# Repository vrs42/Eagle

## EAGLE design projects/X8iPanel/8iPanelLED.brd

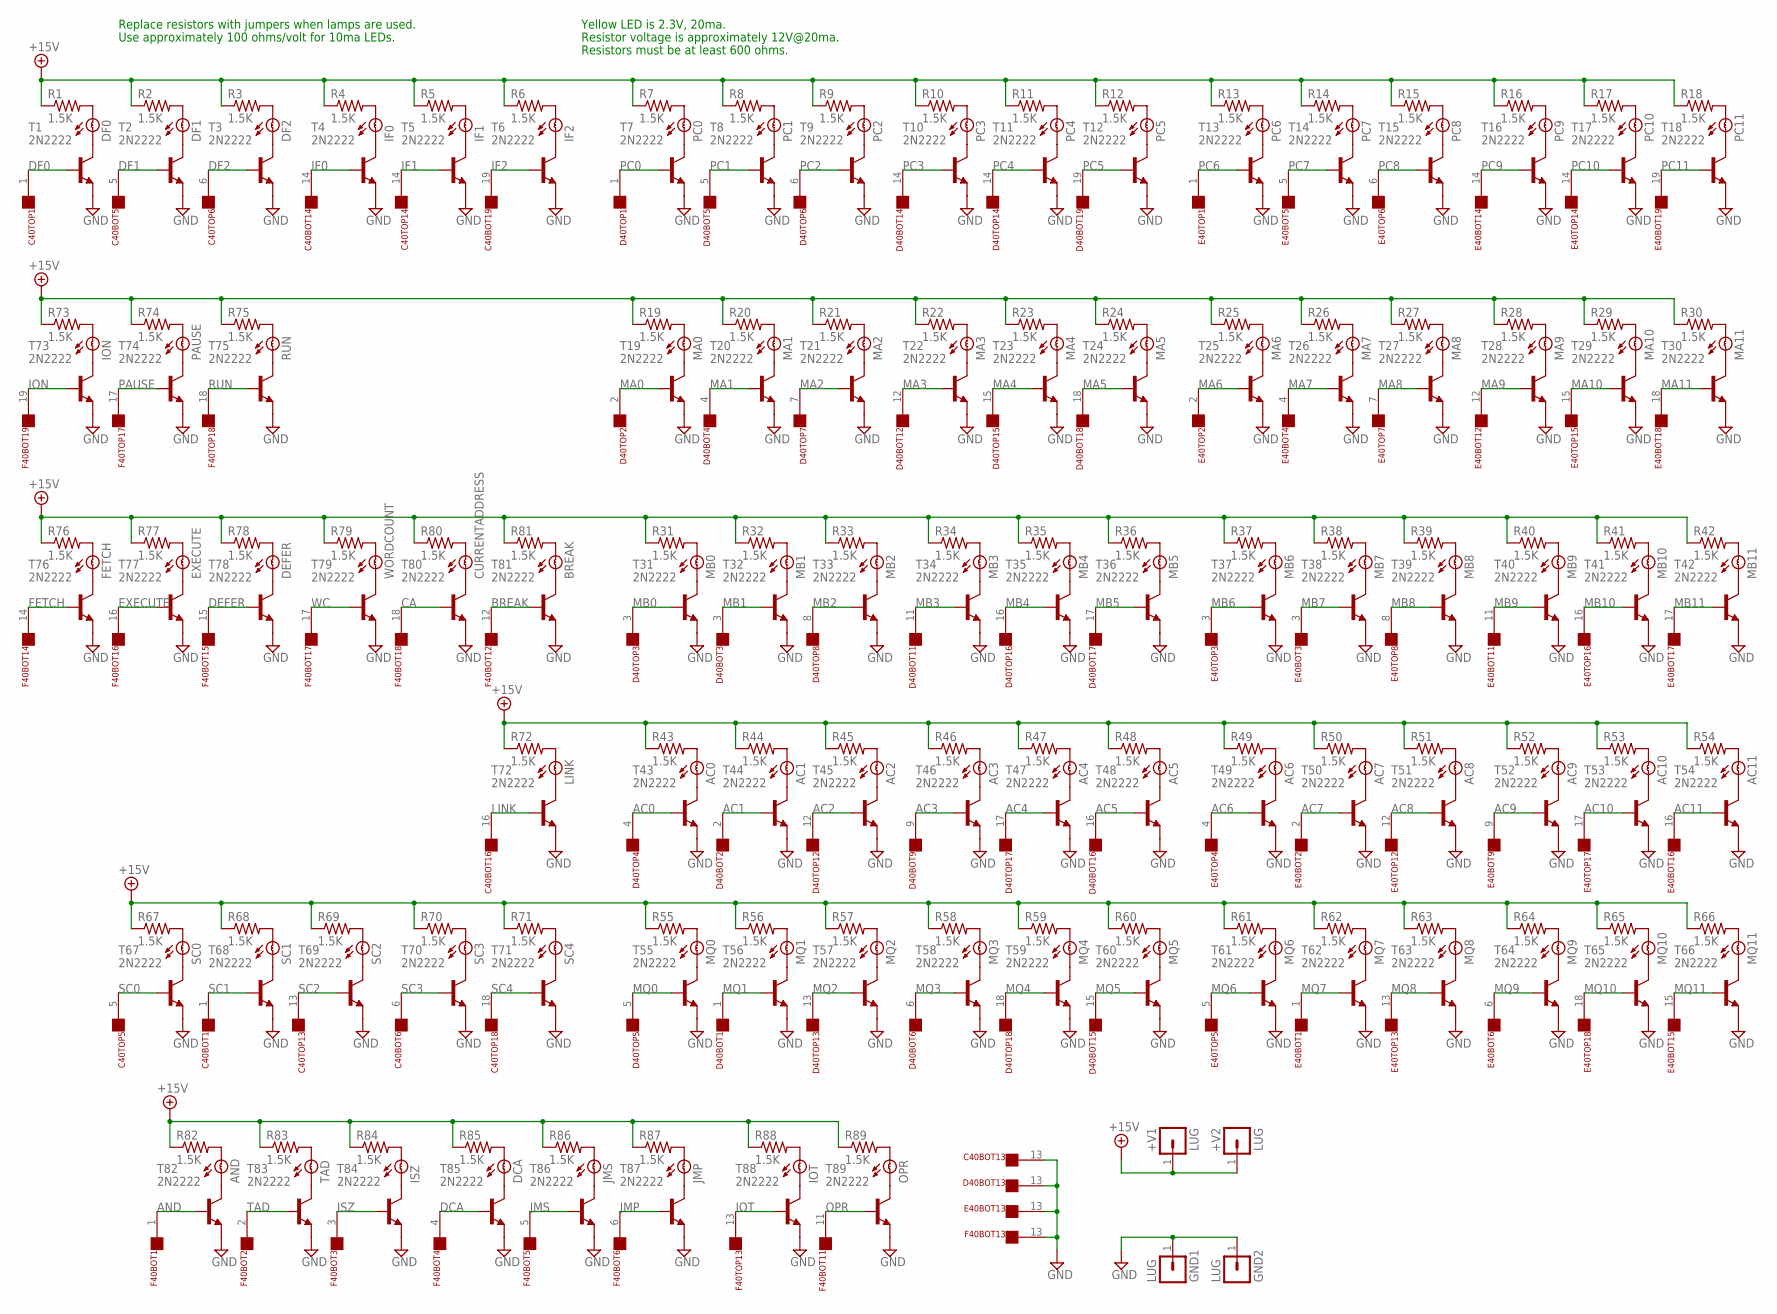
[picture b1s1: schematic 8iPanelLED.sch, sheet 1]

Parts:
+V1, +V2: LUG; SPADELUG
AC0, AC1, AC2, AC3, AC4, AC5, AC6, AC7, AC8, AC9, AC10, AC11: BULB
AND: BULB
BREAK: BULB
C40BOT, C40TOP: FLEX19
CURRENTADDRESS: BULB
D40BOT, D40TOP: FLEX19
DCA: BULB
DEFER: BULB
DF0, DF1, DF2: BULB
E40BOT, E40TOP: FLEX19
EXECUTE: BULB
F40BOT, F40TOP: FLEX19
FETCH: BULB
GND1, GND2: LUG; SPADELUG
IF0, IF1, IF2: BULB
ION: BULB
IOT: BULB
ISZ: BULB
JMP: BULB
JMS: BULB
LINK: BULB
MA0, MA1, MA2, MA3, MA4, MA5, MA6, MA7, MA8, MA9, MA10, MA11: BULB
MB0, MB1, MB2, MB3, MB4, MB5, MB6, MB7, MB8, MB9, MB10, MB11: BULB
MQ0, MQ1, MQ2, MQ3, MQ4, MQ5, MQ6, MQ7, MQ8, MQ9, MQ10, MQ11: BULB
OPR: BULB
PAUSE: BULB
PC0, PC1, PC2, PC3, PC4, PC5, PC6, PC7, PC8, PC9, PC10, PC11: BULB
R1, R2, R3, R4, R5, R6, R7, R8, R9, R10, R11, R12, R13, R14, R15, R16, R17, R18, R19, R20, R21, R22, R23, R24, R25, R26, R27, R28, R29, R30, R31, R32, R33, R34, R35, R36, R37, R38, R39, R40, R41, R42, R43, R44, R45, R46, R47, R48, R49, R50, R51, R52, R53, R54, R55, R56, R57, R58, R59, R60, R61, R62, R63, R64, R65, R66, R67, R68, R69, R70, R71, R72, R73, R74, R75, R76, R77, R78, R79, R80, R81, R82, R83, R84, R85, R86, R87, R88, R89: 1.5K; 0207/10
RUN: BULB
SC0, SC1, SC2, SC3, SC4: BULB
T1, T2, T3, T4, T5, T6, T7, T8, T9, T10, T11, T12, T13, T14, T15, T16, T17, T18, T19, T20, T21, T22, T23, T24, T25, T26, T27, T28, T29, T30, T31, T32, T33, T34, T35, T36, T37, T38, T39, T40, T41, T42, T43, T44, T45, T46, T47, T48, T49, T50, T51, T52, T53, T54, T55, T56, T57, T58, T59, T60, T61, T62, T63, T64, T65, T66, T67, T68, T69, T70, T71, T72, T73, T74, T75, T76, T77, T78, T79, T80, T81, T82, T83, T84, T85, T86, T87, T88, T89: 2N2222; TO92
TAD: BULB
WORDCOUNT: BULB

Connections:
+15V: +V1.1, +V2.1, R1.1, R2.1, R3.1, R4.1, R5.1, R6.1, R7.1, R8.1, R9.1, R10.1, R11.1, R12.1, R13.1, R14.1, R15.1, R16.1, R17.1, R18.1, R19.1, R20.1, R21.1, R22.1, R23.1, R24.1, R25.1, R26.1, R27.1, R28.1, R29.1, R30.1, R31.1, R32.1, R33.1, R34.1, R35.1, R36.1, R37.1, R38.1, R39.1, R40.1, R41.1, R42.1, R43.1, R44.1, R45.1, R46.1, R47.1, R48.1, R49.1, R50.1, R51.1, R52.1, R53.1, R54.1, R55.1, R56.1, R57.1, R58.1, R59.1, R60.1, R61.1, R62.1, R63.1, R64.1, R65.1, R66.1, R67.1, R68.1, R69.1, R70.1, R71.1, R72.1, R73.1, R74.1, R75.1, R76.1, R77.1, R78.1, R79.1, R80.1, R81.1, R82.1, R83.1, R84.1, R85.1, R86.1, R87.1, R88.1, R89.1
AC0: D40TOP.4, T43.2 (B); also elsewhere on the board
AC1: D40BOT.2, T44.2 (B); also elsewhere on the board
AC2: D40TOP.12, T45.2 (B); also elsewhere on the board
AC3: D40BOT.9, T46.2 (B); also elsewhere on the board
AC4: D40TOP.17, T47.2 (B); also elsewhere on the board
AC5: D40BOT.16, T48.2 (B); also elsewhere on the board
AC6: E40TOP.4, T49.2 (B); also elsewhere on the board
AC7: E40BOT.2, T50.2 (B); also elsewhere on the board
AC8: E40TOP.12, T51.2 (B); also elsewhere on the board
AC9: E40BOT.9, T52.2 (B); also elsewhere on the board
AC10: E40TOP.17, T53.2 (B); also elsewhere on the board
AC11: E40BOT.16, T54.2 (B); also elsewhere on the board
AND: F40BOT.1, T82.2 (B); also elsewhere on the board
BREAK: F40BOT.12, T81.2 (B); also elsewhere on the board
CA: F40BOT.18, T80.2 (B); also elsewhere on the board
DCA: F40BOT.4, T85.2 (B); also elsewhere on the board
DEFER: F40BOT.15, T78.2 (B); also elsewhere on the board
DF0: C40TOP.1, T1.2 (B); also elsewhere on the board
DF1: C40BOT.5, T2.2 (B); also elsewhere on the board
DF2: C40TOP.6, T3.2 (B); also elsewhere on the board
EXECUTE: F40BOT.16, T77.2 (B); also elsewhere on the board
FETCH: F40BOT.14, T76.2 (B); also elsewhere on the board
GND: C40BOT.13, D40BOT.13, E40BOT.13, F40BOT.13, GND1.1, GND2.1, T1.1 (E), T2.1 (E), T3.1 (E), T4.1 (E), T5.1 (E), T6.1 (E), T7.1 (E), T8.1 (E), T9.1 (E), T10.1 (E), T11.1 (E), T12.1 (E), T13.1 (E), T14.1 (E), T15.1 (E), T16.1 (E), T17.1 (E), T18.1 (E), T19.1 (E), T20.1 (E), T21.1 (E), T22.1 (E), T23.1 (E), T24.1 (E), T25.1 (E), T26.1 (E), T27.1 (E), T28.1 (E), T29.1 (E), T30.1 (E), T31.1 (E), T32.1 (E), T33.1 (E), T34.1 (E), T35.1 (E), T36.1 (E), T37.1 (E), T38.1 (E), T39.1 (E), T40.1 (E), T41.1 (E), T42.1 (E), T43.1 (E), T44.1 (E), T45.1 (E), T46.1 (E), T47.1 (E), T48.1 (E), T49.1 (E), T50.1 (E), T51.1 (E), T52.1 (E), T53.1 (E), T54.1 (E), T55.1 (E), T56.1 (E), T57.1 (E), T58.1 (E), T59.1 (E), T60.1 (E), T61.1 (E), T62.1 (E), T63.1 (E), T64.1 (E), T65.1 (E), T66.1 (E), T67.1 (E), T68.1 (E), T69.1 (E), T70.1 (E), T71.1 (E), T72.1 (E), T73.1 (E), T74.1 (E), T75.1 (E), T76.1 (E), T77.1 (E), T78.1 (E), T79.1 (E), T80.1 (E), T81.1 (E), T82.1 (E), T83.1 (E), T84.1 (E), T85.1 (E), T86.1 (E), T87.1 (E), T88.1 (E), T89.1 (E); also elsewhere on the board
IF0: C40BOT.14, T4.2 (B); also elsewhere on the board
IF1: C40TOP.14, T5.2 (B); also elsewhere on the board
IF2: C40BOT.19, T6.2 (B); also elsewhere on the board
ION: F40BOT.19, T73.2 (B); also elsewhere on the board
IOT: F40TOP.13, T88.2 (B); also elsewhere on the board
ISZ: F40BOT.3, T84.2 (B); also elsewhere on the board
JMP: F40BOT.6, T87.2 (B); also elsewhere on the board
JMS: F40BOT.5, T86.2 (B); also elsewhere on the board
LINK: C40BOT.16, T72.2 (B); also elsewhere on the board
MA0: D40TOP.2, T19.2 (B); also elsewhere on the board
MA1: D40BOT.4, T20.2 (B); also elsewhere on the board
MA2: D40TOP.7, T21.2 (B); also elsewhere on the board
MA3: D40BOT.12, T22.2 (B); also elsewhere on the board
MA4: D40TOP.15, T23.2 (B); also elsewhere on the board
MA5: D40BOT.18, T24.2 (B); also elsewhere on the board
MA6: E40TOP.2, T25.2 (B); also elsewhere on the board
MA7: E40BOT.4, T26.2 (B); also elsewhere on the board
MA8: E40TOP.7, T27.2 (B); also elsewhere on the board
MA9: E40BOT.12, T28.2 (B); also elsewhere on the board
MA10: E40TOP.15, T29.2 (B); also elsewhere on the board
MA11: E40BOT.18, T30.2 (B); also elsewhere on the board
MB0: D40TOP.3, T31.2 (B); also elsewhere on the board
MB1: D40BOT.3, T32.2 (B); also elsewhere on the board
MB2: D40TOP.8, T33.2 (B); also elsewhere on the board
MB3: D40BOT.11, T34.2 (B); also elsewhere on the board
MB4: D40TOP.16, T35.2 (B); also elsewhere on the board
MB5: D40BOT.17, T36.2 (B); also elsewhere on the board
MB6: E40TOP.3, T37.2 (B); also elsewhere on the board
MB7: E40BOT.3, T38.2 (B); also elsewhere on the board
MB8: E40TOP.8, T39.2 (B); also elsewhere on the board
MB9: E40BOT.11, T40.2 (B); also elsewhere on the board
MB10: E40TOP.16, T41.2 (B); also elsewhere on the board
MB11: E40BOT.17, T42.2 (B); also elsewhere on the board
MQ0: D40TOP.5, T55.2 (B); also elsewhere on the board
MQ1: D40BOT.1, T56.2 (B); also elsewhere on the board
MQ2: D40TOP.13, T57.2 (B); also elsewhere on the board
MQ3: D40BOT.6, T58.2 (B); also elsewhere on the board
MQ4: D40TOP.18, T59.2 (B); also elsewhere on the board
MQ5: D40BOT.15, T60.2 (B); also elsewhere on the board
MQ6: E40TOP.5, T61.2 (B); also elsewhere on the board
MQ7: E40BOT.1, T62.2 (B); also elsewhere on the board
MQ8: E40TOP.13, T63.2 (B); also elsewhere on the board
MQ9: E40BOT.6, T64.2 (B); also elsewhere on the board
MQ10: E40TOP.18, T65.2 (B); also elsewhere on the board
MQ11: E40BOT.15, T66.2 (B); also elsewhere on the board
unnamed: DF0.B, T1.3 (C)
unnamed: DF1.B, T2.3 (C)
unnamed: DF2.B, T3.3 (C)
unnamed: IF0.B, T4.3 (C)
unnamed: IF1.B, T5.3 (C)
unnamed: IF2.B, T6.3 (C)
unnamed: PC0.B, T7.3 (C)
unnamed: PC1.B, T8.3 (C)
unnamed: PC2.B, T9.3 (C)
unnamed: PC3.B, T10.3 (C)
unnamed: PC4.B, T11.3 (C)
unnamed: PC5.B, T12.3 (C)
unnamed: PC6.B, T13.3 (C)
unnamed: PC7.B, T14.3 (C)
unnamed: PC8.B, T15.3 (C)
unnamed: PC9.B, T16.3 (C)
unnamed: PC10.B, T17.3 (C)
unnamed: PC11.B, T18.3 (C)
unnamed: MA0.B, T19.3 (C)
unnamed: MA1.B, T20.3 (C)
unnamed: MA2.B, T21.3 (C)
unnamed: MA3.B, T22.3 (C)
unnamed: MA4.B, T23.3 (C)
unnamed: MA5.B, T24.3 (C)
unnamed: MA6.B, T25.3 (C)
unnamed: MA7.B, T26.3 (C)
unnamed: MA8.B, T27.3 (C)
unnamed: MA9.B, T28.3 (C)
unnamed: MA10.B, T29.3 (C)
unnamed: MA11.B, T30.3 (C)
unnamed: MB0.B, T31.3 (C)
unnamed: MB1.B, T32.3 (C)
unnamed: MB2.B, T33.3 (C)
unnamed: MB3.B, T34.3 (C)
unnamed: MB4.B, T35.3 (C)
unnamed: MB5.B, T36.3 (C)
unnamed: MB6.B, T37.3 (C)
unnamed: MB7.B, T38.3 (C)
unnamed: MB8.B, T39.3 (C)
unnamed: MB9.B, T40.3 (C)
unnamed: MB10.B, T41.3 (C)
unnamed: MB11.B, T42.3 (C)
unnamed: AC0.B, T43.3 (C)
unnamed: AC1.B, T44.3 (C)
unnamed: AC2.B, T45.3 (C)
unnamed: AC3.B, T46.3 (C)
unnamed: AC4.B, T47.3 (C)
unnamed: AC5.B, T48.3 (C)
unnamed: AC6.B, T49.3 (C)
unnamed: AC7.B, T50.3 (C)
unnamed: AC8.B, T51.3 (C)
unnamed: AC9.B, T52.3 (C)
unnamed: AC10.B, T53.3 (C)
unnamed: AC11.B, T54.3 (C)
unnamed: MQ0.B, T55.3 (C)
unnamed: MQ1.B, T56.3 (C)
unnamed: MQ2.B, T57.3 (C)
unnamed: MQ3.B, T58.3 (C)
unnamed: MQ4.B, T59.3 (C)
unnamed: MQ5.B, T60.3 (C)
unnamed: MQ6.B, T61.3 (C)
unnamed: MQ7.B, T62.3 (C)
unnamed: MQ8.B, T63.3 (C)
unnamed: MQ9.B, T64.3 (C)
unnamed: MQ10.B, T65.3 (C)
unnamed: MQ11.B, T66.3 (C)
unnamed: SC0.B, T67.3 (C)
unnamed: SC1.B, T68.3 (C)
unnamed: SC2.B, T69.3 (C)
unnamed: SC3.B, T70.3 (C)
unnamed: SC4.B, T71.3 (C)
unnamed: LINK.B, T72.3 (C)
unnamed: ION.B, T73.3 (C)
unnamed: PAUSE.B, T74.3 (C)
unnamed: RUN.B, T75.3 (C)
unnamed: FETCH.B, T76.3 (C)
unnamed: EXECUTE.B, T77.3 (C)
unnamed: DEFER.B, T78.3 (C)
unnamed: T79.3 (C), WORDCOUNT.B
unnamed: CURRENTADDRESS.B, T80.3 (C)
unnamed: BREAK.B, T81.3 (C)
unnamed: AND.B, T82.3 (C)
unnamed: T83.3 (C), TAD.B
unnamed: ISZ.B, T84.3 (C)
unnamed: DCA.B, T85.3 (C)
unnamed: JMS.B, T86.3 (C)
unnamed: JMP.B, T87.3 (C)
unnamed: IOT.B, T88.3 (C)
unnamed: OPR.B, T89.3 (C)
unnamed: DF0.A, R1.2
unnamed: DF1.A, R2.2
unnamed: DF2.A, R3.2
unnamed: IF0.A, R4.2
unnamed: IF1.A, R5.2
unnamed: IF2.A, R6.2
unnamed: PC0.A, R7.2
unnamed: PC1.A, R8.2
unnamed: PC2.A, R9.2
unnamed: PC3.A, R10.2
unnamed: PC4.A, R11.2
unnamed: PC5.A, R12.2
unnamed: PC6.A, R13.2
unnamed: PC7.A, R14.2
unnamed: PC8.A, R15.2
unnamed: PC9.A, R16.2
unnamed: PC10.A, R17.2
unnamed: PC11.A, R18.2
unnamed: ION.A, R73.2
unnamed: PAUSE.A, R74.2
unnamed: R75.2, RUN.A
unnamed: MA0.A, R19.2
unnamed: MA1.A, R20.2
unnamed: MA2.A, R21.2
unnamed: MA3.A, R22.2
unnamed: MA4.A, R23.2
unnamed: MA5.A, R24.2
unnamed: MA6.A, R25.2
unnamed: MA7.A, R26.2
unnamed: MA8.A, R27.2
unnamed: MA9.A, R28.2
unnamed: MA10.A, R29.2
unnamed: MA11.A, R30.2
unnamed: FETCH.A, R76.2
unnamed: EXECUTE.A, R77.2
unnamed: DEFER.A, R78.2
unnamed: R79.2, WORDCOUNT.A
unnamed: CURRENTADDRESS.A, R80.2
unnamed: BREAK.A, R81.2
unnamed: LINK.A, R72.2
unnamed: MB0.A, R31.2
unnamed: MB1.A, R32.2
unnamed: MB2.A, R33.2
unnamed: MB3.A, R34.2
unnamed: MB4.A, R35.2
unnamed: MB5.A, R36.2
unnamed: MB6.A, R37.2
unnamed: MB7.A, R38.2
unnamed: MB8.A, R39.2
unnamed: MB9.A, R40.2
unnamed: MB10.A, R41.2
unnamed: MB11.A, R42.2
unnamed: AC0.A, R43.2
unnamed: AC1.A, R44.2
unnamed: AC2.A, R45.2
unnamed: AC3.A, R46.2
unnamed: AC4.A, R47.2
unnamed: AC5.A, R48.2
unnamed: AC6.A, R49.2
unnamed: AC7.A, R50.2
unnamed: AC8.A, R51.2
unnamed: AC9.A, R52.2
unnamed: AC10.A, R53.2
unnamed: AC11.A, R54.2
unnamed: R67.2, SC0.A
unnamed: R68.2, SC1.A
unnamed: R69.2, SC2.A
unnamed: R70.2, SC3.A
unnamed: R71.2, SC4.A
unnamed: MQ11.A, R66.2
unnamed: MQ10.A, R65.2
unnamed: MQ9.A, R64.2
unnamed: MQ8.A, R63.2
unnamed: MQ7.A, R62.2
unnamed: MQ6.A, R61.2
unnamed: MQ5.A, R60.2
unnamed: MQ4.A, R59.2
unnamed: MQ3.A, R58.2
unnamed: MQ2.A, R57.2
unnamed: MQ1.A, R56.2
unnamed: MQ0.A, R55.2
unnamed: AND.A, R82.2
unnamed: R83.2, TAD.A
unnamed: ISZ.A, R84.2
unnamed: DCA.A, R85.2
unnamed: JMS.A, R86.2
unnamed: JMP.A, R87.2
unnamed: IOT.A, R88.2
unnamed: OPR.A, R89.2
OPR: F40BOT.11, T89.2 (B); also elsewhere on the board
PAUSE: F40TOP.17, T74.2 (B); also elsewhere on the board
PC0: D40TOP.1, T7.2 (B); also elsewhere on the board
PC1: D40BOT.5, T8.2 (B); also elsewhere on the board
PC2: D40TOP.6, T9.2 (B); also elsewhere on the board
PC3: D40BOT.14, T10.2 (B); also elsewhere on the board
PC4: D40TOP.14, T11.2 (B); also elsewhere on the board
PC5: D40BOT.19, T12.2 (B); also elsewhere on the board
PC6: E40TOP.1, T13.2 (B); also elsewhere on the board
PC7: E40BOT.5, T14.2 (B); also elsewhere on the board
PC8: E40TOP.6, T15.2 (B); also elsewhere on the board
PC9: E40BOT.14, T16.2 (B); also elsewhere on the board
PC10: E40TOP.14, T17.2 (B); also elsewhere on the board
PC11: E40BOT.19, T18.2 (B); also elsewhere on the board
RUN: F40TOP.18, T75.2 (B); also elsewhere on the board
SC0: C40TOP.5, T67.2 (B); also elsewhere on the board
SC1: C40BOT.1, T68.2 (B); also elsewhere on the board
SC2: C40TOP.13, T69.2 (B); also elsewhere on the board
SC3: C40BOT.6, T70.2 (B); also elsewhere on the board
SC4: C40TOP.18, T71.2 (B); also elsewhere on the board
TAD: F40BOT.2, T83.2 (B); also elsewhere on the board
WC: F40BOT.17, T79.2 (B); also elsewhere on the board

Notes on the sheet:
Replace resistors with jumpers when lamps are used.
Use approximately 100 ohms/volt for 10ma LEDs.
Yellow LED is 2.3V, 20ma.
Resistor voltage is approximately 12V@20ma.
Resistors must be at least 600 ohms.

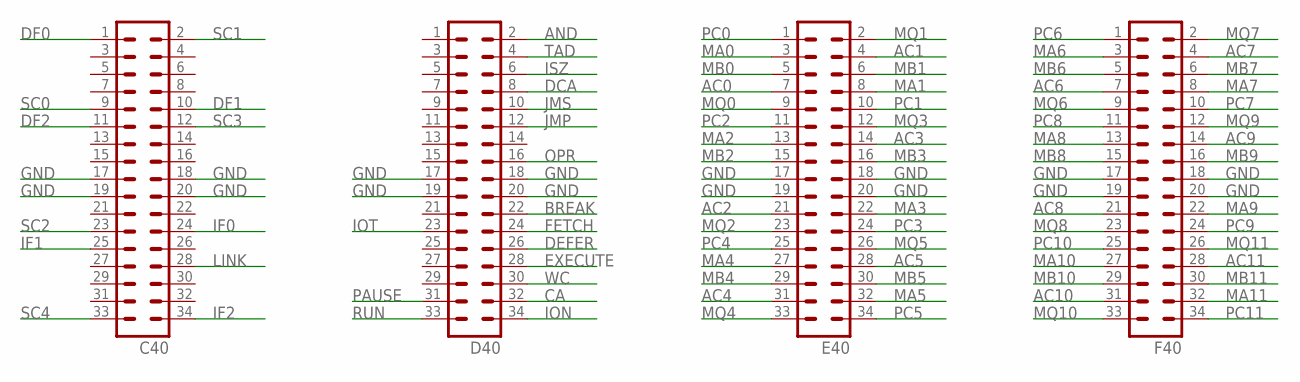
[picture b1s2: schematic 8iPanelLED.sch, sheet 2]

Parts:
C40: MA17-2
D40: MA17-2
E40: MA17-2
F40: MA17-2

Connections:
AC0: E40.7; also elsewhere on the board
AC1: E40.4; also elsewhere on the board
AC2: E40.21; also elsewhere on the board
AC3: E40.14; also elsewhere on the board
AC4: E40.31; also elsewhere on the board
AC5: E40.28; also elsewhere on the board
AC6: F40.7; also elsewhere on the board
AC7: F40.4; also elsewhere on the board
AC8: F40.21; also elsewhere on the board
AC9: F40.14; also elsewhere on the board
AC10: F40.31; also elsewhere on the board
AC11: F40.28; also elsewhere on the board
AND: D40.2; also elsewhere on the board
BREAK: D40.22; also elsewhere on the board
CA: D40.32; also elsewhere on the board
DCA: D40.8; also elsewhere on the board
DEFER: D40.26; also elsewhere on the board
DF0: C40.1; also elsewhere on the board
DF1: C40.10; also elsewhere on the board
DF2: C40.11; also elsewhere on the board
EXECUTE: D40.28; also elsewhere on the board
FETCH: D40.24; also elsewhere on the board
GND: C40.17, C40.18, C40.19, C40.20, D40.17, D40.18, D40.19, D40.20, E40.17, E40.18, E40.19, E40.20, F40.17, F40.18, F40.19, F40.20; also elsewhere on the board
IF0: C40.24; also elsewhere on the board
IF1: C40.25; also elsewhere on the board
IF2: C40.34; also elsewhere on the board
ION: D40.34; also elsewhere on the board
IOT: D40.23; also elsewhere on the board
ISZ: D40.6; also elsewhere on the board
JMP: D40.12; also elsewhere on the board
JMS: D40.10; also elsewhere on the board
LINK: C40.28; also elsewhere on the board
MA0: E40.3; also elsewhere on the board
MA1: E40.8; also elsewhere on the board
MA2: E40.13; also elsewhere on the board
MA3: E40.22; also elsewhere on the board
MA4: E40.27; also elsewhere on the board
MA5: E40.32; also elsewhere on the board
MA6: F40.3; also elsewhere on the board
MA7: F40.8; also elsewhere on the board
MA8: F40.13; also elsewhere on the board
MA9: F40.22; also elsewhere on the board
MA10: F40.27; also elsewhere on the board
MA11: F40.32; also elsewhere on the board
MB0: E40.5; also elsewhere on the board
MB1: E40.6; also elsewhere on the board
MB2: E40.15; also elsewhere on the board
MB3: E40.16; also elsewhere on the board
MB4: E40.29; also elsewhere on the board
MB5: E40.30; also elsewhere on the board
MB6: F40.5; also elsewhere on the board
MB7: F40.6; also elsewhere on the board
MB8: F40.15; also elsewhere on the board
MB9: F40.16; also elsewhere on the board
MB10: F40.29; also elsewhere on the board
MB11: F40.30; also elsewhere on the board
MQ0: E40.9; also elsewhere on the board
MQ1: E40.2; also elsewhere on the board
MQ2: E40.23; also elsewhere on the board
MQ3: E40.12; also elsewhere on the board
MQ4: E40.33; also elsewhere on the board
MQ5: E40.26; also elsewhere on the board
MQ6: F40.9; also elsewhere on the board
MQ7: F40.2; also elsewhere on the board
MQ8: F40.23; also elsewhere on the board
MQ9: F40.12; also elsewhere on the board
MQ10: F40.33; also elsewhere on the board
MQ11: F40.26; also elsewhere on the board
OPR: D40.16; also elsewhere on the board
PAUSE: D40.31; also elsewhere on the board
PC0: E40.1; also elsewhere on the board
PC1: E40.10; also elsewhere on the board
PC2: E40.11; also elsewhere on the board
PC3: E40.24; also elsewhere on the board
PC4: E40.25; also elsewhere on the board
PC5: E40.34; also elsewhere on the board
PC6: F40.1; also elsewhere on the board
PC7: F40.10; also elsewhere on the board
PC8: F40.11; also elsewhere on the board
PC9: F40.24; also elsewhere on the board
PC10: F40.25; also elsewhere on the board
PC11: F40.34; also elsewhere on the board
RUN: D40.33; also elsewhere on the board
SC0: C40.9; also elsewhere on the board
SC1: C40.2; also elsewhere on the board
SC2: C40.23; also elsewhere on the board
SC3: C40.12; also elsewhere on the board
SC4: C40.33; also elsewhere on the board
TAD: D40.4; also elsewhere on the board
WC: D40.30; also elsewhere on the board

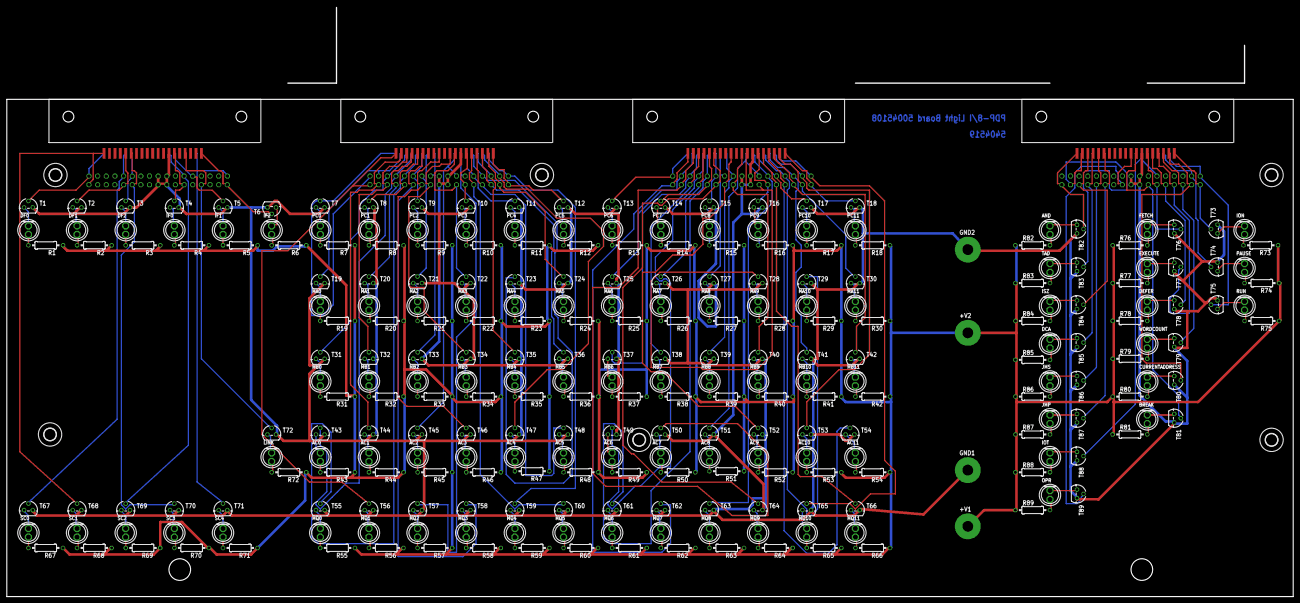
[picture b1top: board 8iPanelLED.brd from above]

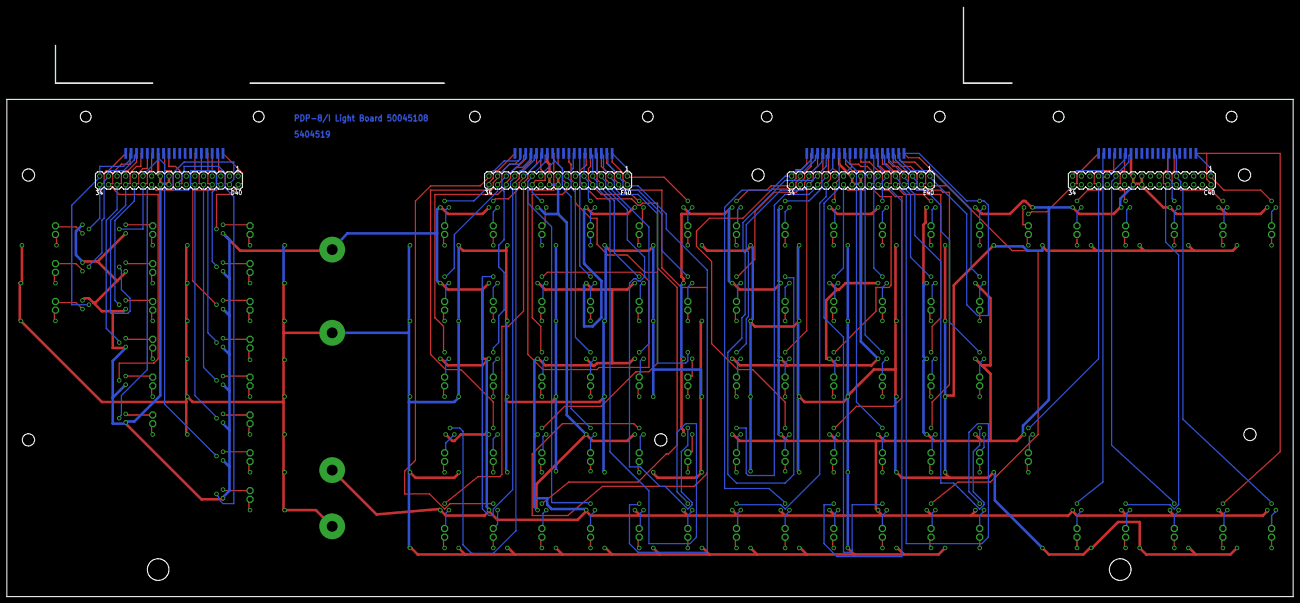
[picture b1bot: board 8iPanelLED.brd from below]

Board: 2 copper layers, 377.8 x 146.1 mm, 293 parts (8 on the bottom side), 269 nets.

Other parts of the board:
U$1, U$2, U$3, U$4: STRAIN-RELIEF
U$5, U$6, U$7, U$8, U$9, U$11: 3,6

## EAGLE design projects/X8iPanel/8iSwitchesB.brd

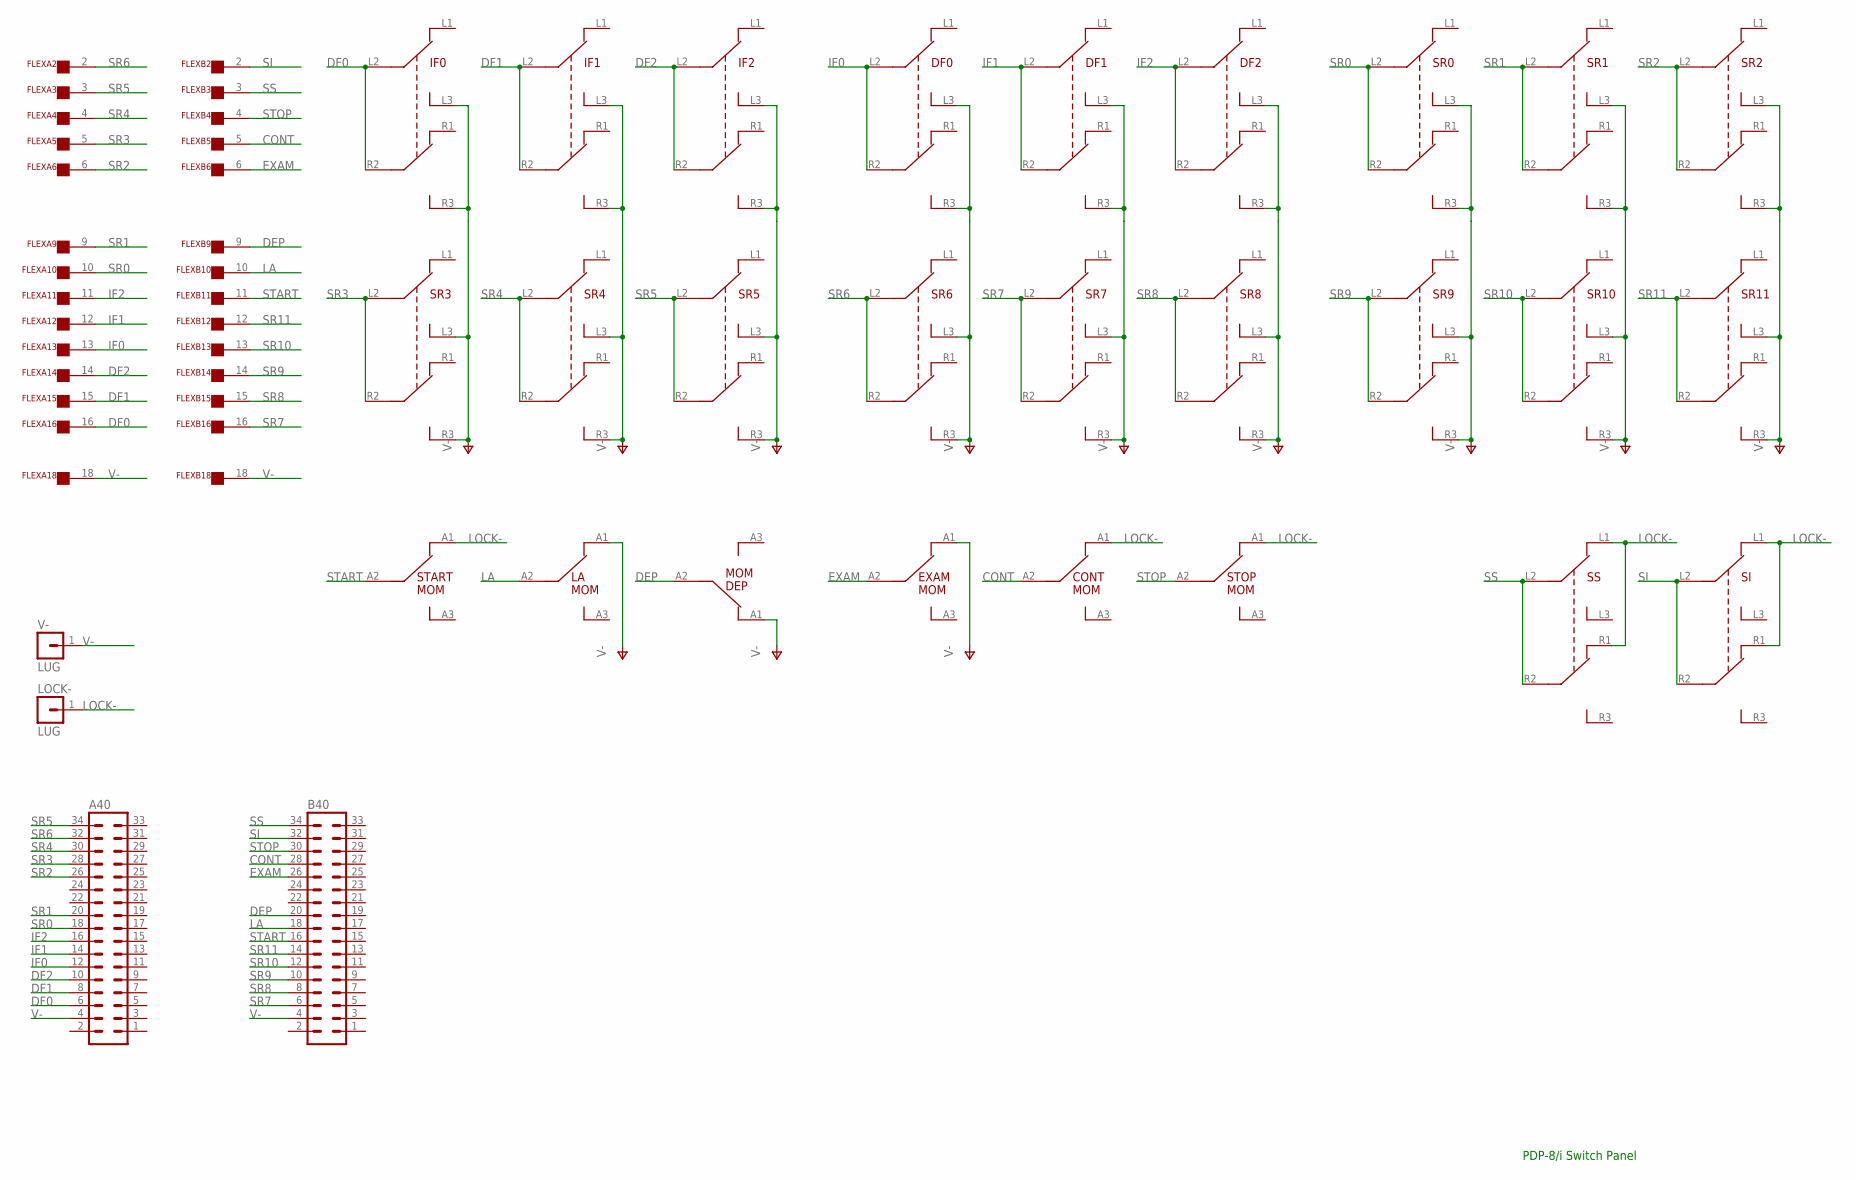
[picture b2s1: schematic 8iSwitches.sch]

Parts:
A40: MA17-2
B40: MA17-2
CONT: SPDT8I
DEP: SPDT8I
DF0, DF1, DF2: DPDT8I
EXAM: SPDT8I
FLEXA: FLEX19
FLEXB: FLEX19
IF0, IF1, IF2: DPDT8I
LA: SPDT8I
LOCK-: LUG; SPADELUG
SI: DPDT8I
SR0, SR1, SR2, SR3, SR4, SR5, SR6, SR7, SR8, SR9, SR10, SR11: DPDT8I
SS: DPDT8I
START: SPDT8I
STOP: SPDT8I
V-: LUG; SPADELUG

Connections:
CONT: B40.28, CONT.A2, FLEXB.5
DEP: B40.20, DEP.A2, FLEXB.9
DF0: A40.6, FLEXA.16, IF0.L2 (A2), IF0.R2 (B2)
DF1: A40.8, FLEXA.15, IF1.L2 (A2), IF1.R2 (B2)
DF2: A40.10, FLEXA.14, IF2.L2 (A2), IF2.R2 (B2)
EXAM: B40.26, EXAM.A2, FLEXB.6
IF0: A40.12, DF0.L2 (A2), DF0.R2 (B2), FLEXA.13
IF1: A40.14, DF1.L2 (A2), DF1.R2 (B2), FLEXA.12
IF2: A40.16, DF2.L2 (A2), DF2.R2 (B2), FLEXA.11
LA: B40.18, FLEXB.10, LA.A2
LOCK-: CONT.A1, LOCK-.1, SI.L1 (A1), SI.R1 (B1), SS.L1 (A1), SS.R1 (B1), START.A1, STOP.A1
SI: B40.32, FLEXB.2, SI.L2 (A2), SI.R2 (B2)
SR0: A40.18, FLEXA.10, SR0.L2 (A2), SR0.R2 (B2)
SR1: A40.20, FLEXA.9, SR1.L2 (A2), SR1.R2 (B2)
SR2: A40.26, FLEXA.6, SR2.L2 (A2), SR2.R2 (B2)
SR3: A40.28, FLEXA.5, SR3.L2 (A2), SR3.R2 (B2)
SR4: A40.30, FLEXA.4, SR4.L2 (A2), SR4.R2 (B2)
SR5: A40.34, FLEXA.3, SR5.L2 (A2), SR5.R2 (B2)
SR6: A40.32, FLEXA.2, SR6.L2 (A2), SR6.R2 (B2)
SR7: B40.6, FLEXB.16, SR7.L2 (A2), SR7.R2 (B2)
SR8: B40.8, FLEXB.15, SR8.L2 (A2), SR8.R2 (B2)
SR9: B40.10, FLEXB.14, SR9.L2 (A2), SR9.R2 (B2)
SR10: B40.12, FLEXB.13, SR10.L2 (A2), SR10.R2 (B2)
SR11: B40.14, FLEXB.12, SR11.L2 (A2), SR11.R2 (B2)
SS: B40.34, FLEXB.3, SS.L2 (A2), SS.R2 (B2)
START: B40.16, FLEXB.11, START.A2
STOP: B40.30, FLEXB.4, STOP.A2
V-: A40.4, B40.4, DEP.A1, DF0.L3 (A3), DF0.R3 (B3), DF1.L3 (A3), DF1.R3 (B3), DF2.L3 (A3), DF2.R3 (B3), EXAM.A1, FLEXA.18, FLEXB.18, IF0.L3 (A3), IF0.R3 (B3), IF1.L3 (A3), IF1.R3 (B3), IF2.L3 (A3), IF2.R3 (B3), LA.A1, SR0.L3 (A3), SR0.R3 (B3), SR1.L3 (A3), SR1.R3 (B3), SR2.L3 (A3), SR2.R3 (B3), SR3.L3 (A3), SR3.R3 (B3), SR4.L3 (A3), SR4.R3 (B3), SR5.L3 (A3), SR5.R3 (B3), SR6.L3 (A3), SR6.R3 (B3), SR7.L3 (A3), SR7.R3 (B3), SR8.L3 (A3), SR8.R3 (B3), SR9.L3 (A3), SR9.R3 (B3), SR10.L3 (A3), SR10.R3 (B3), SR11.L3 (A3), SR11.R3 (B3), V-.1

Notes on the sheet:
PDP-8/i Switch Panel

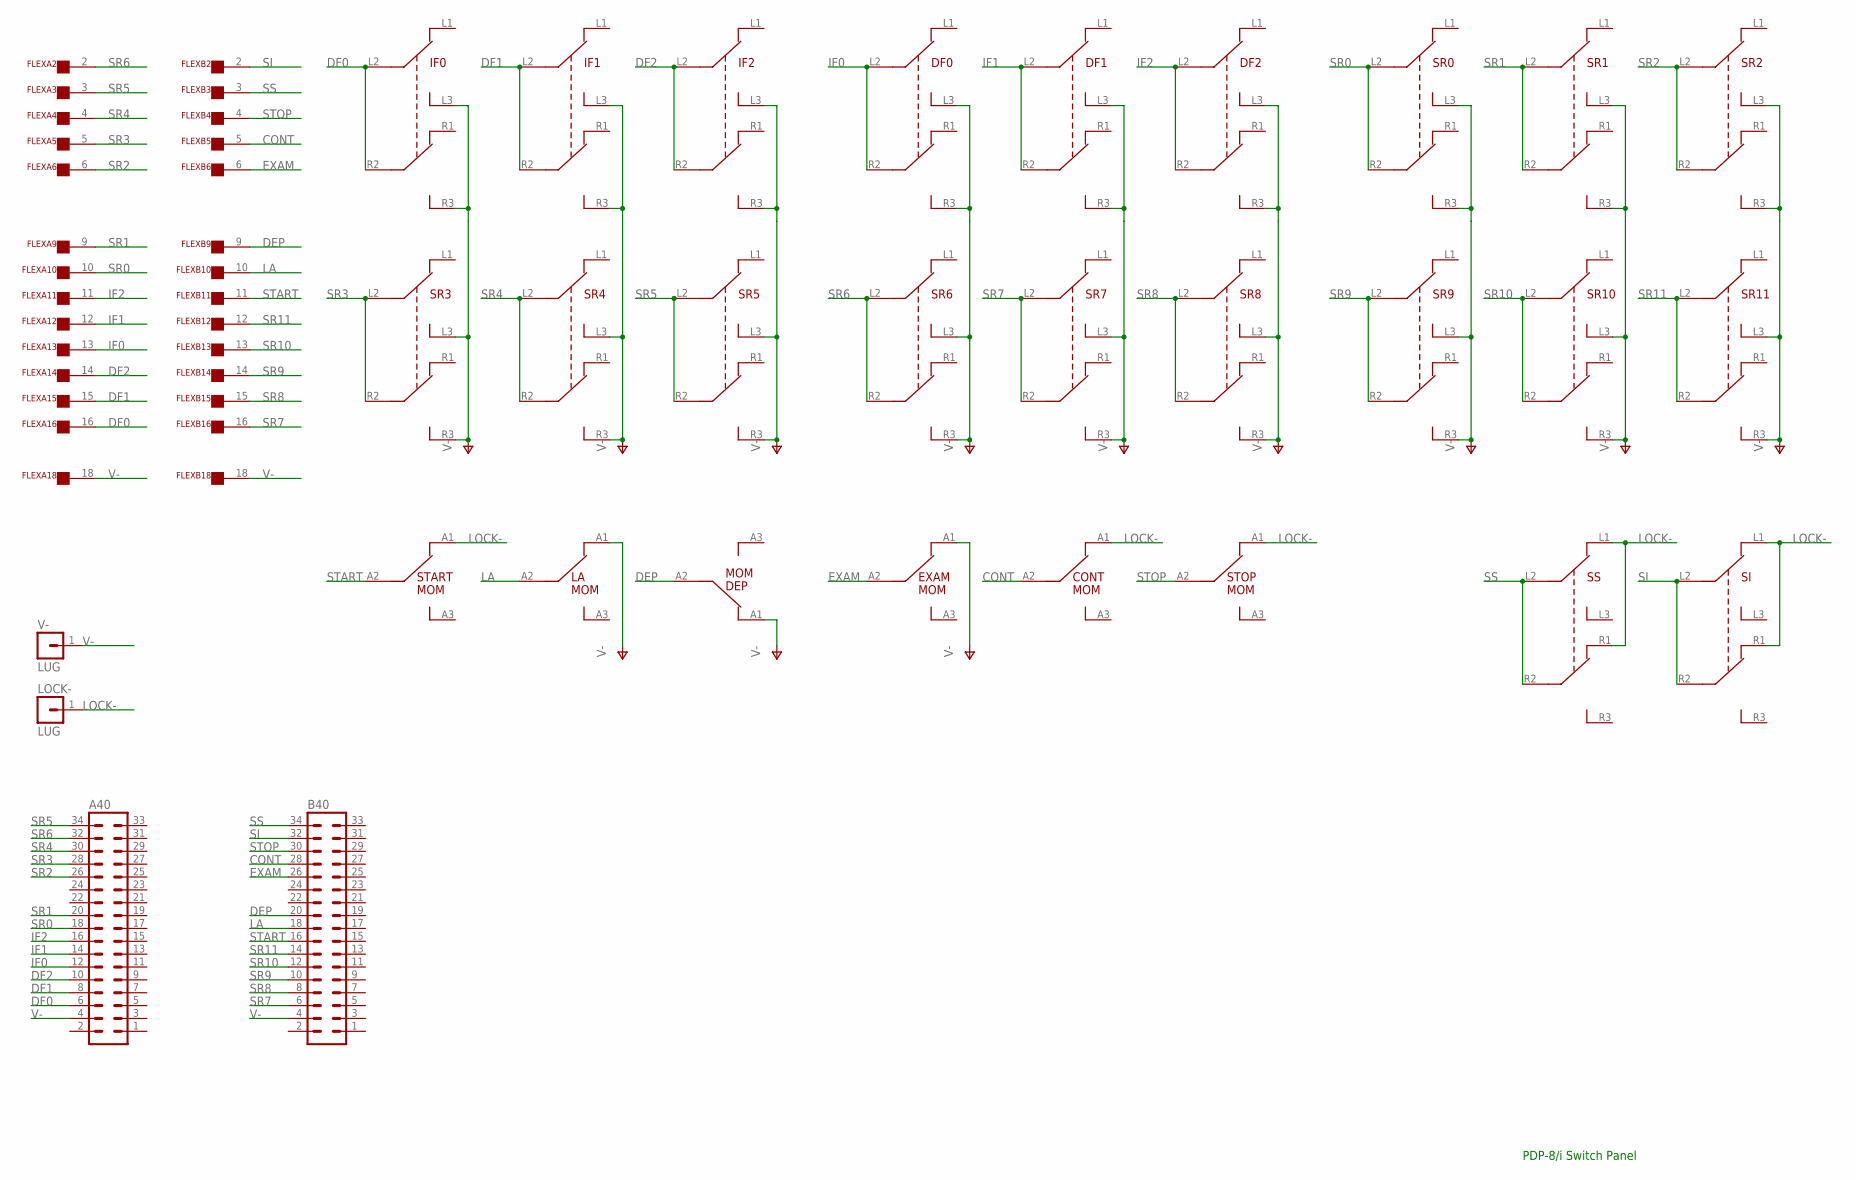
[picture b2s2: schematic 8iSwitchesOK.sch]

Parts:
A40: MA17-2
B40: MA17-2
CONT: SPDT8I
DEP: SPDT8I
DF0, DF1, DF2: DPDT8I
EXAM: SPDT8I
FLEXA: FLEX19
FLEXB: FLEX19
IF0, IF1, IF2: DPDT8I
LA: SPDT8I
LOCK-: LUG; SPADELUG
SI: DPDT8I
SR0, SR1, SR2, SR3, SR4, SR5, SR6, SR7, SR8, SR9, SR10, SR11: DPDT8I
SS: DPDT8I
START: SPDT8I
STOP: SPDT8I
V-: LUG; SPADELUG

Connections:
CONT: B40.28, CONT.A2, FLEXB.5
DEP: B40.20, DEP.A2, FLEXB.9
DF0: A40.6, FLEXA.16, IF0.L2 (A2), IF0.R2 (B2)
DF1: A40.8, FLEXA.15, IF1.L2 (A2), IF1.R2 (B2)
DF2: A40.10, FLEXA.14, IF2.L2 (A2), IF2.R2 (B2)
EXAM: B40.26, EXAM.A2, FLEXB.6
IF0: A40.12, DF0.L2 (A2), DF0.R2 (B2), FLEXA.13
IF1: A40.14, DF1.L2 (A2), DF1.R2 (B2), FLEXA.12
IF2: A40.16, DF2.L2 (A2), DF2.R2 (B2), FLEXA.11
LA: B40.18, FLEXB.10, LA.A2
LOCK-: CONT.A1, LOCK-.1, SI.L1 (A1), SI.R1 (B1), SS.L1 (A1), SS.R1 (B1), START.A1, STOP.A1
SI: B40.32, FLEXB.2, SI.L2 (A2), SI.R2 (B2)
SR0: A40.18, FLEXA.10, SR0.L2 (A2), SR0.R2 (B2)
SR1: A40.20, FLEXA.9, SR1.L2 (A2), SR1.R2 (B2)
SR2: A40.26, FLEXA.6, SR2.L2 (A2), SR2.R2 (B2)
SR3: A40.28, FLEXA.5, SR3.L2 (A2), SR3.R2 (B2)
SR4: A40.30, FLEXA.4, SR4.L2 (A2), SR4.R2 (B2)
SR5: A40.34, FLEXA.3, SR5.L2 (A2), SR5.R2 (B2)
SR6: A40.32, FLEXA.2, SR6.L2 (A2), SR6.R2 (B2)
SR7: B40.6, FLEXB.16, SR7.L2 (A2), SR7.R2 (B2)
SR8: B40.8, FLEXB.15, SR8.L2 (A2), SR8.R2 (B2)
SR9: B40.10, FLEXB.14, SR9.L2 (A2), SR9.R2 (B2)
SR10: B40.12, FLEXB.13, SR10.L2 (A2), SR10.R2 (B2)
SR11: B40.14, FLEXB.12, SR11.L2 (A2), SR11.R2 (B2)
SS: B40.34, FLEXB.3, SS.L2 (A2), SS.R2 (B2)
START: B40.16, FLEXB.11, START.A2
STOP: B40.30, FLEXB.4, STOP.A2
V-: A40.4, B40.4, DEP.A1, DF0.L3 (A3), DF0.R3 (B3), DF1.L3 (A3), DF1.R3 (B3), DF2.L3 (A3), DF2.R3 (B3), EXAM.A1, FLEXA.18, FLEXB.18, IF0.L3 (A3), IF0.R3 (B3), IF1.L3 (A3), IF1.R3 (B3), IF2.L3 (A3), IF2.R3 (B3), LA.A1, SR0.L3 (A3), SR0.R3 (B3), SR1.L3 (A3), SR1.R3 (B3), SR2.L3 (A3), SR2.R3 (B3), SR3.L3 (A3), SR3.R3 (B3), SR4.L3 (A3), SR4.R3 (B3), SR5.L3 (A3), SR5.R3 (B3), SR6.L3 (A3), SR6.R3 (B3), SR7.L3 (A3), SR7.R3 (B3), SR8.L3 (A3), SR8.R3 (B3), SR9.L3 (A3), SR9.R3 (B3), SR10.L3 (A3), SR10.R3 (B3), SR11.L3 (A3), SR11.R3 (B3), V-.1

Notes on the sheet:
PDP-8/i Switch Panel

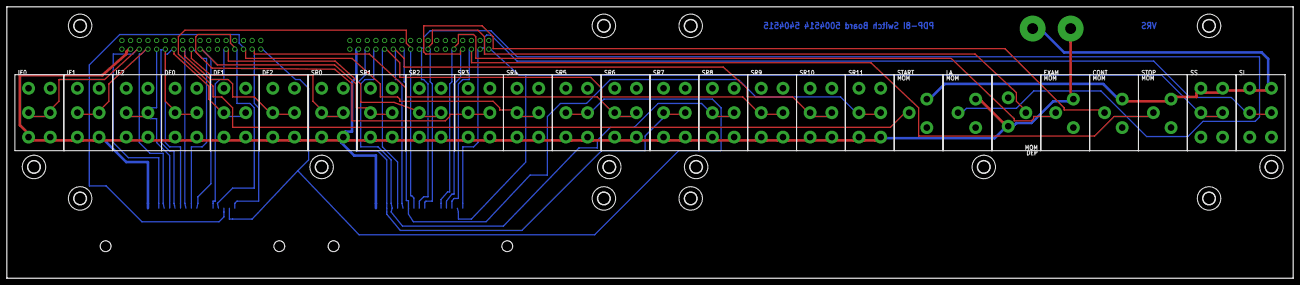
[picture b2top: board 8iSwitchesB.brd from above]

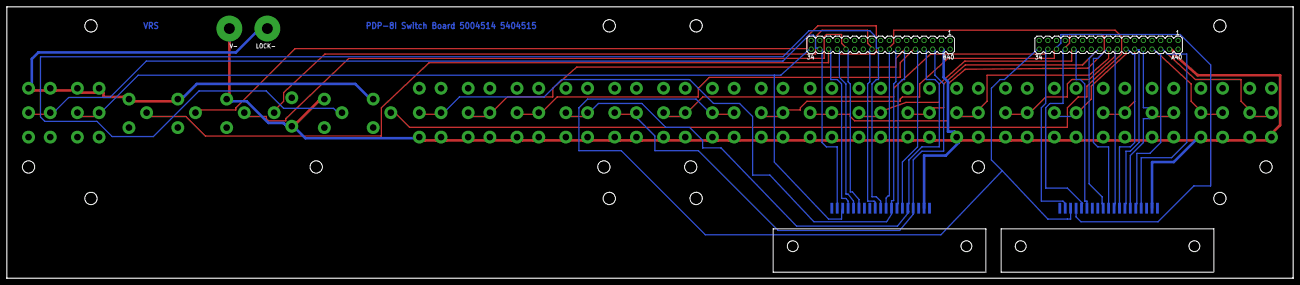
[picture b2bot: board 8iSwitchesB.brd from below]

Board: 2 copper layers, 376.2 x 79.4 mm, 48 parts (8 on the bottom side), 28 nets.

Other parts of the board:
U$1, U$2, U$3, U$4, U$5, U$6, U$7, U$10, U$11, U$12, U$13, U$14, U$15, U$16: 3,6
U$17, U$18: STRAIN-RELIEF
